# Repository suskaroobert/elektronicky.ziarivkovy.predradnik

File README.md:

# Oprava Pro'sKit Magnifier Lamp Neon

---

Potom čo mi odišla do večných lovísk moja neónka, som sa rozhodol, že ju zreparujem. Inšpiráciu som najprv hľadal na konferencii [Hw-list][hwlist] kde ma jeden príspevok naviedol na slovo predradník. Síce som chvíľku uvažoval o tom, že žiarivku nahradím LED diódami, ale toto riešenie som ihneď zavrhol, keď som objavil na stránke [https://danyk.cz/][danyk]

[Elektronický zářivkový předřadník 8 - 144W][danykpredradnikcz]

Jeho stavba skončila úspešne, za čo som autorovi veľmi vďačný.

Moje riešenie spočíva v tom, že som schému prekreslil do programu EAGLE a navrhol na DPS, ktorý vojde do otvoru pre pôvodnú elektroniku lampy.

## Poznámky ku stavbe

Rezistor R2 je počas prevádzky veľmi horúci. Vytiahol som ho preto mimo priestor lampy, do malej krabičky z hliníkového plechu. Z vrchu a od spodu sú v krabičke navŕtané otvory pre lepšie chladenie rezistoru.

Ďalej, pôvodný prívodný kábel bol len dvojžilový, tak som ho vymenil za trojžilový a kryt svietidla a krabičku s rezistorom som uzemnil.

## ENG version

After my fluorescent tubes went to the eternal hunting grounds, I decided to repair it. I first looked for inspiration on the [Hw-list][hwlist] mailing list, where a post led me to the word ballast. Although I briefly considered replacing the fluorescent bulb with LEDs, I immediately dismissed this solution when I discovered on the site [https://danyk.cz/][danyk]

[Electronic ballast for fluorescent tubes 8 - 144W][danykpredradnikeng]

Its construction ended successfully, for which I am very grateful to the author.

My solution was to redraw the schematic in EAGLE and design a PCB that fits into the hole for the original lamp electronics.

## Notes on the building

Resistor R2 is very hot during operation. I therefore pulled it out of the lamp compartment, into a small box made of aluminum sheet. There are holes drilled in the box from the top and bottom for better cooling of the resistor.

Next, the original supply cable was only two-wire, so I replaced it with a three-wire one and grounded the lamp cover and the resistor box.

[hwlist]: https://list.hw.cz/mailman/listinfo/hw-list
[danyk]: https://danyk.cz/
[danykpredradnikcz]: https://danyk.cz/zarivk_p.html
[danykpredradnikeng]: https://danyk.cz/zarivk_p_en.html

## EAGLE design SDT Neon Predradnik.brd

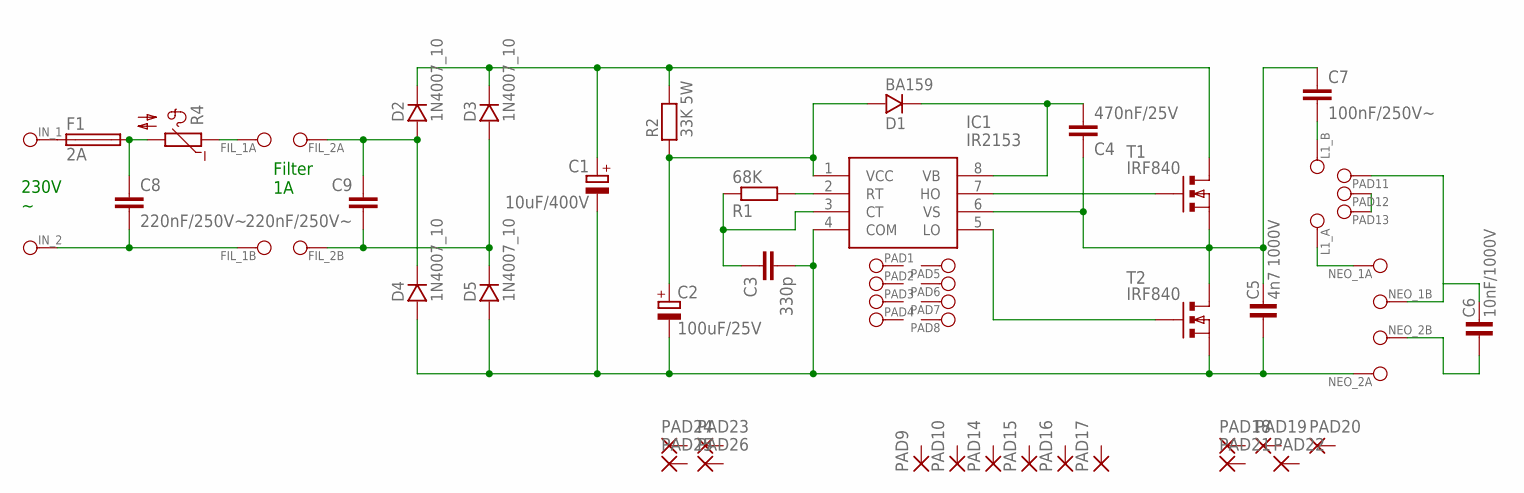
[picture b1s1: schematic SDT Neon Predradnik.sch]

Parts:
C1: 10uF/400V; ELEKTROLITICKY_RM5-10
C2: 100uF/25V; ELEKTROLITICKY_RM2,5-6,3
C3: 330p; KERAMICKY_RM5
C4: 470nF/25V; FOLIOVY_RM5/3,5-7,2
C5: 4n7 1000V; C-7,5
C6: 10nF/1000V; C-10
C7: 100nF/250V~; FOLIOVY_RM15/5-18
C8, C9: 220nF/250V~; FOLIOVY_RM15/5-18
D1: BA159; D-10
D2, D3, D4, D5: 1N4007_10; D-10
F1: 2A; TE5
FIL_1A, FIL_1B, FIL_2A, FIL_2B: PAD_1---
IC1: IR2153; DIP762W56P254L988H533Q8N
IN_1, IN_2: IN_~_1; PAD_1---
L1_A, L1_B: PAD_1---
NEO_1A, NEO_1B, NEO_2A, NEO_2B: PAD_1---
PAD1, PAD2, PAD3, PAD4, PAD5, PAD6, PAD7, PAD8, PAD11, PAD12, PAD13: PAD_1---
PAD9, PAD10, PAD14, PAD15, PAD16, PAD17: 3,81/1,3
PAD18, PAD19, PAD20, PAD21, PAD22, PAD23, PAD24, PAD25, PAD26: 2,54/1,1
R1: 68K; 0204/5
R2: 33K 5W; R-_5W
R4: NTC644C; N644C
T1, T2: IRF840; TO-220S

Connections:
unnamed: F1.1, IN_1.1
unnamed: C8.P$1 (1), F1.2, R4.2
unnamed: C8.P$2 (2), FIL_1B.1, IN_2.1
unnamed: FIL_1A.1, R4.1
unnamed: C9.P$1 (1), D2.A, D4.K, FIL_2A.1
unnamed: IC1.7 (HO), T1.1 (G)
unnamed: C1.P$2 (+), D2.K, D3.K, R2.2, T1.2 (D)
unnamed: C6.2, NEO_1B.1, PAD11.1
unnamed: IC1.5 (LO), T2.1 (G)
unnamed: C4.P$2 (2), D1.K, IC1.8 (VB)
unnamed: IC1.2 (RT), R1.2
unnamed: C3.P$1 (1), IC1.3 (CT), R1.1
unnamed: C4.P$1 (1), C5.2, C7.P$1 (1), IC1.6 (VS), T1.3 (S), T2.2 (D)
unnamed: C1.P$1 (-), C2.P$1 (-), C3.P$2 (2), C5.1, D4.A, D5.A, IC1.4 (COM), NEO_2A.1, T2.3 (S)
unnamed: C2.P$2 (+), D1.A, IC1.1 (VCC), R2.1
unnamed: C7.P$2 (2), L1_B.1
unnamed: C6.1, NEO_2B.1
unnamed: L1_A.1, NEO_1A.1
unnamed: C9.P$2 (2), D3.A, D5.K, FIL_2B.1
unnamed: PAD12.1, PAD13.1

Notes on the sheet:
230V ~
Filter 1A

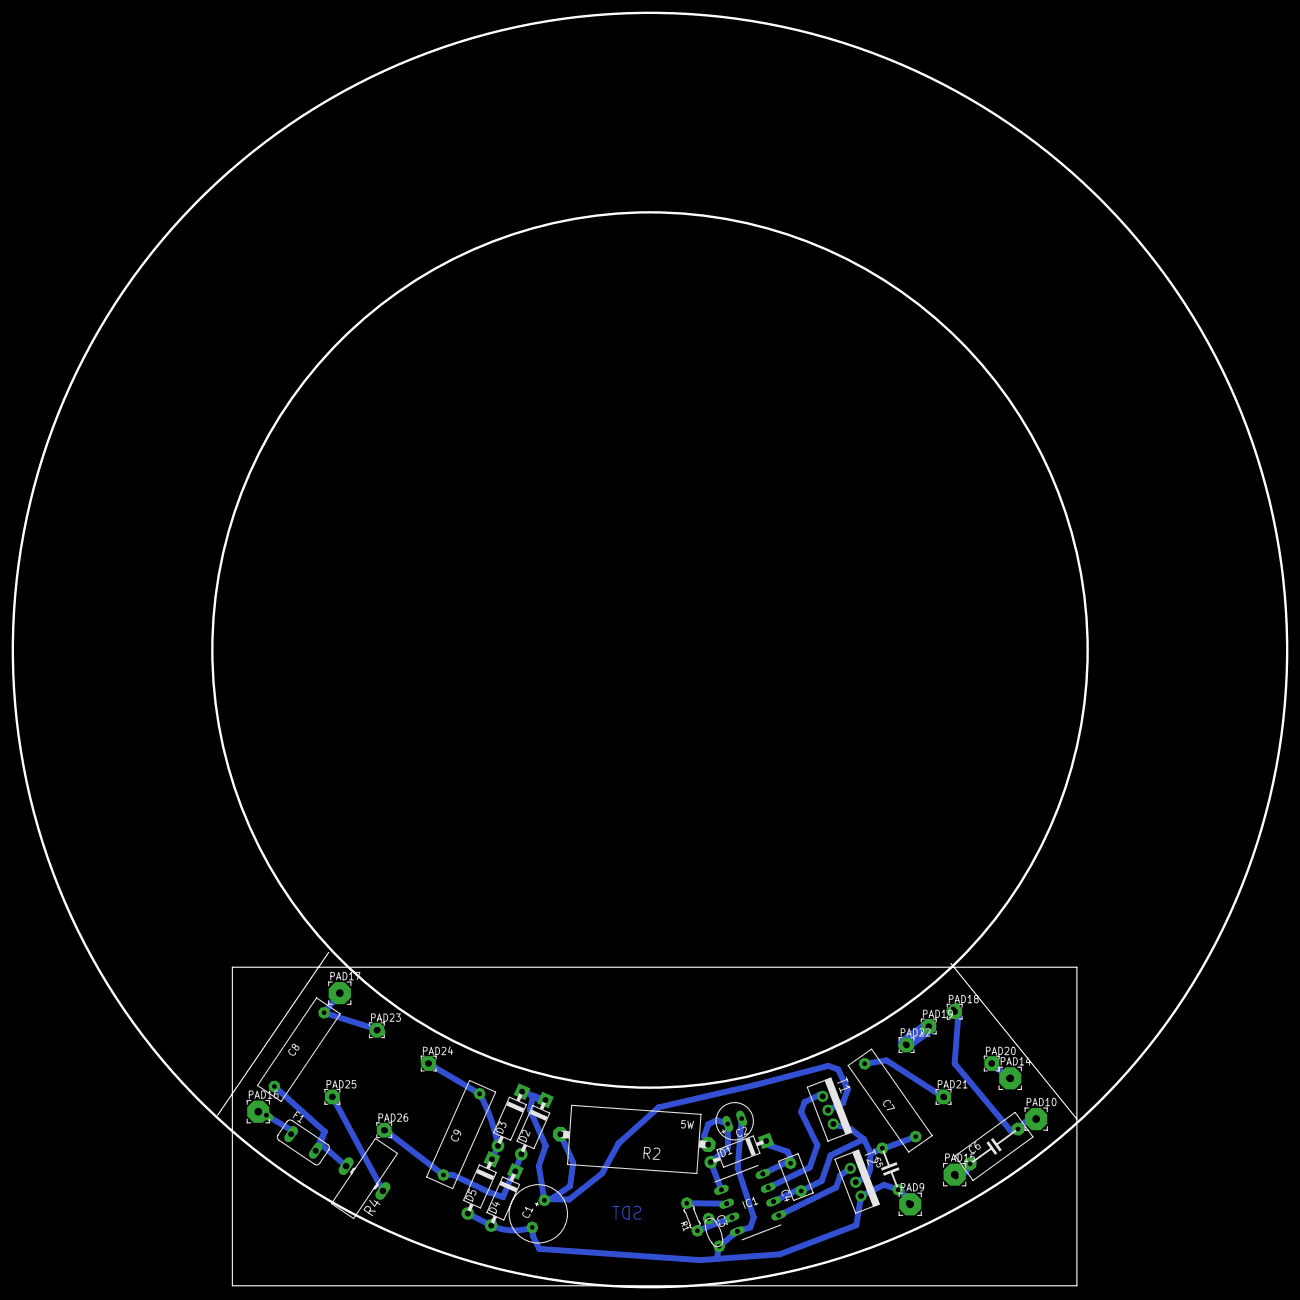
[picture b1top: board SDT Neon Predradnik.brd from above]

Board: 2 copper layers, 218.5 x 218.5 mm, 59 parts (0 on the bottom side), 20 nets.

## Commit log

2025-05-23 - prvy
2025-05-23 - zmena gridu
2025-05-25 - final
2025-05-25 - pridal som fotku krabičky s rezistorom R2 - pridal som README.md súbor
2025-05-25 - UTF8 fix

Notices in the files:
parts and their libraries:
Copyright (C) Vlada 2004-2005
Copyright (C) PaJa 2001-2005
